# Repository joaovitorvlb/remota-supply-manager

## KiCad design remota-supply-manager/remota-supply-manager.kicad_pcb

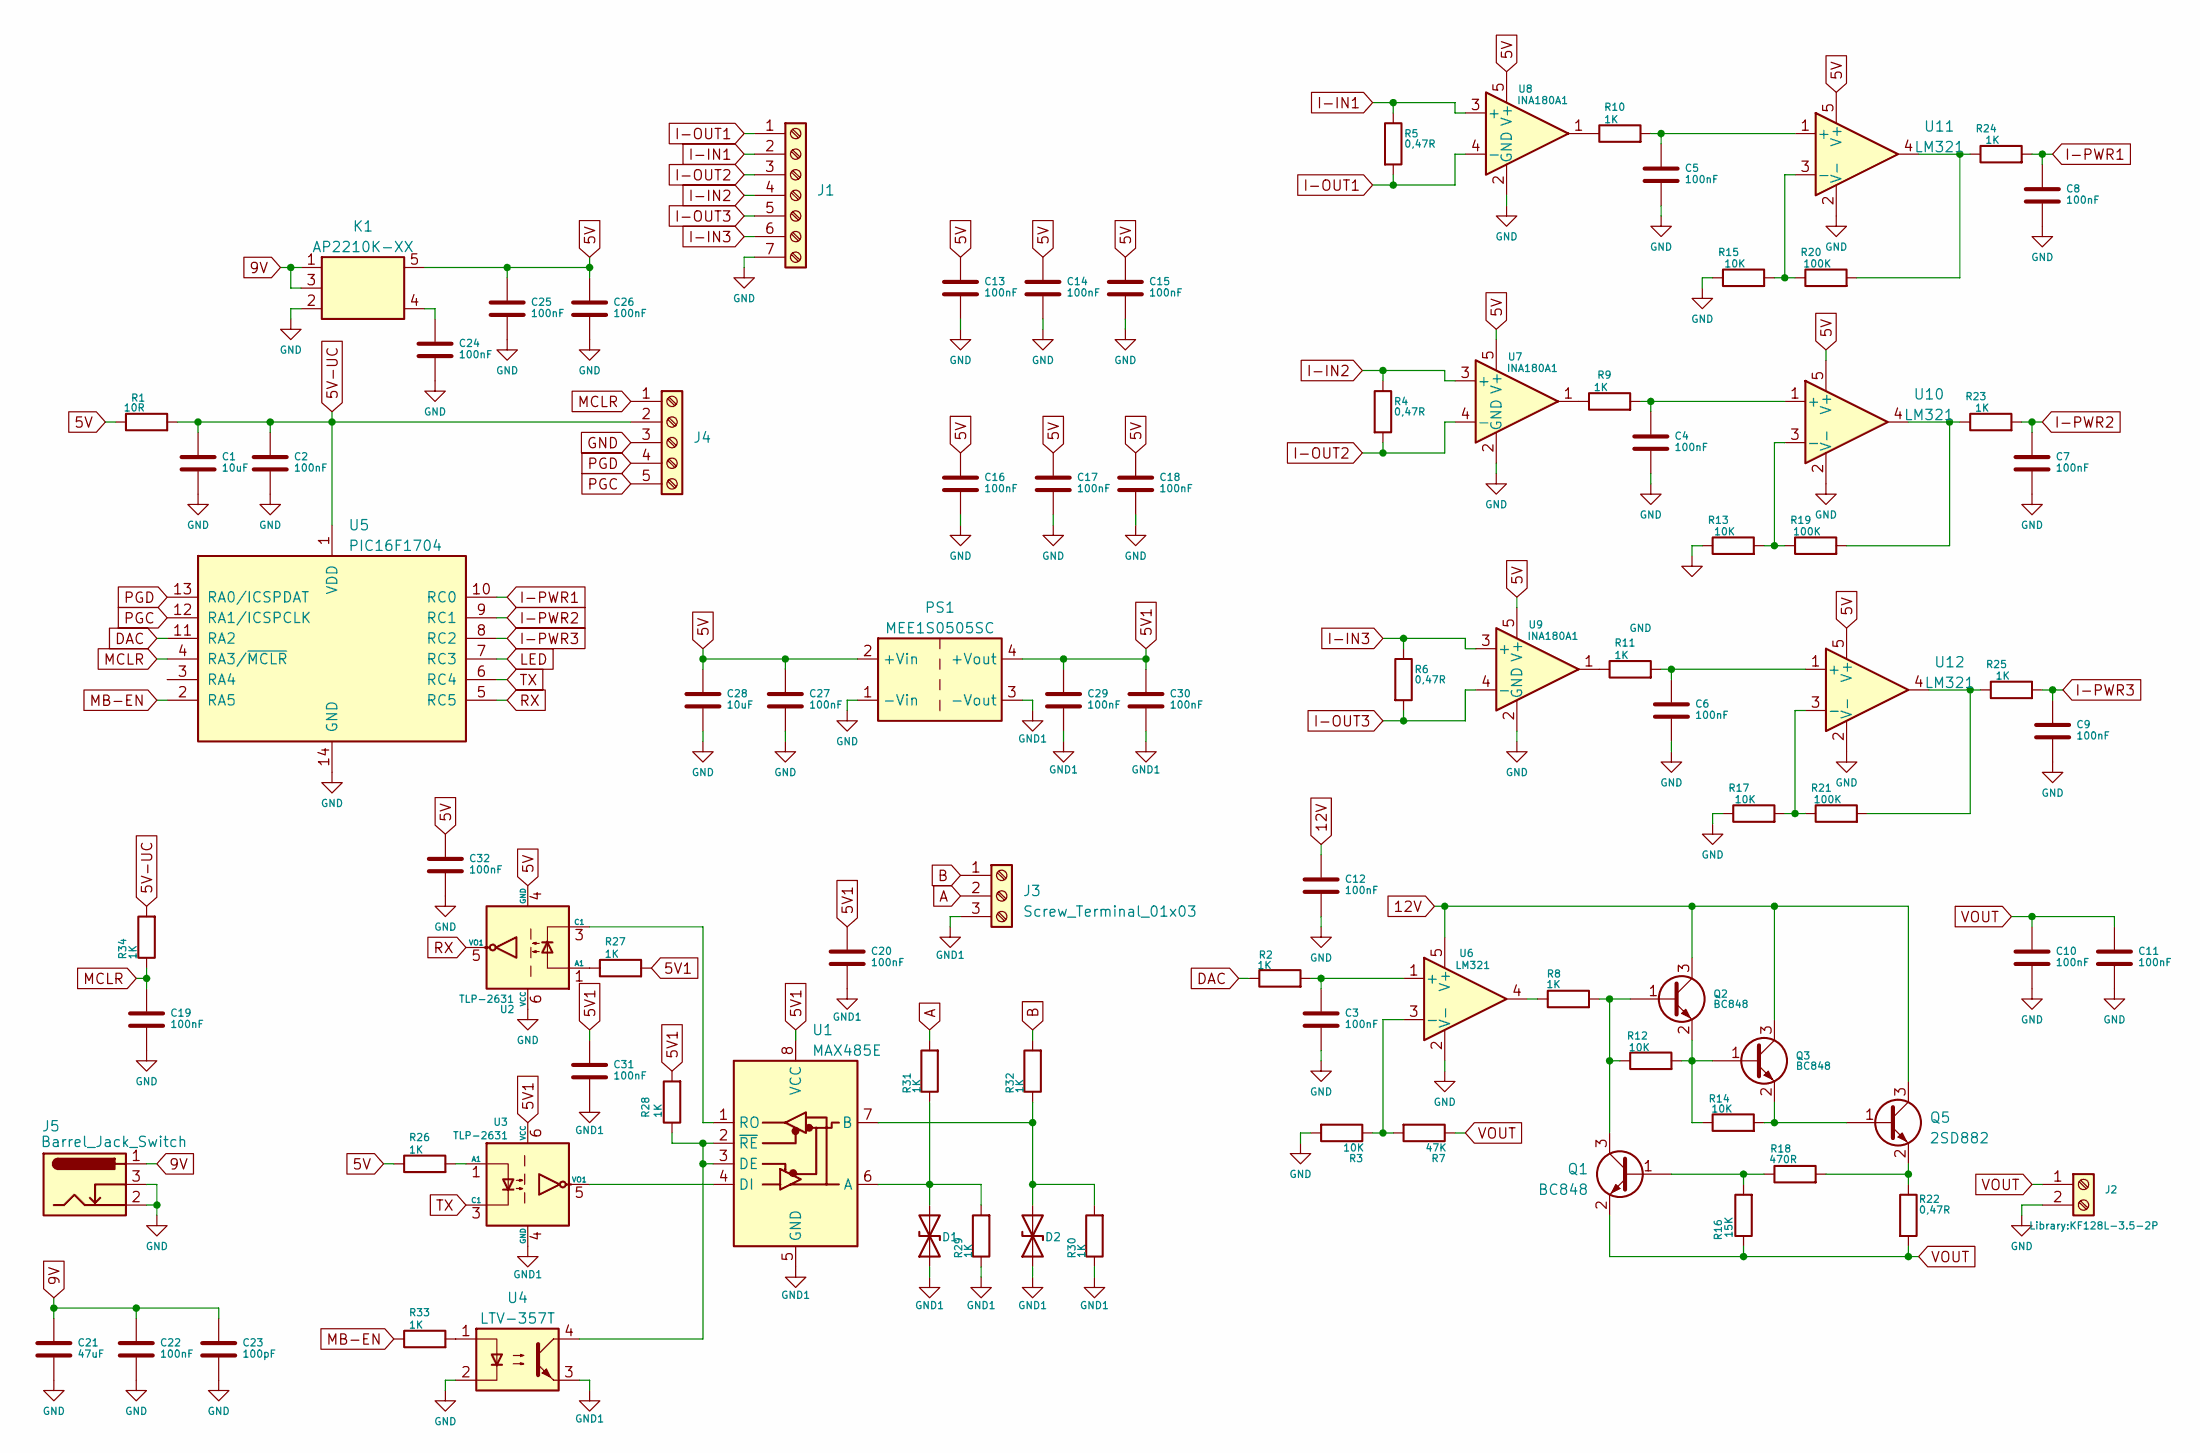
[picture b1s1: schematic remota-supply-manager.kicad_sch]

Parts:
C1, C28: 10uF; C_0805_2012Metric
C2, C3, C4, C5, C6, C7, C8, C9, C10, C11, C12, C13, C14, C15, C16, C17, C18, C19, C20, C22, C24, C25, C26, C27, C29, C30, C31, C32: 100nF; C_0805_2012Metric
C21: 47uF; C_1210_3225Metric
C23: 100pF; C_0805_2012Metric
D1, D2: D_TVS; D_SOD-128
J1: Screw_Terminal_01x07; KF128L-3.5-7P
J2: Screw_Terminal_01x02; KF128L-3.5-2P
J3: Screw_Terminal_01x03; KF128L-3.5-3P
J4: Screw_Terminal_01x05; PinHeader_1x05_P2.54mm_Vertical
J5: Barrel_Jack_Switch; BarrelJack_GCT_DCJ200-10-A_Horizontal
K1: AP2210K-XX; SOT-23-5
PS1: MEE1S0505SC; Converter_DCDC_Murata_MEE1SxxxxSC_THT
Q1, Q2, Q3: BC848; SOT-23
Q5: 2SD882; TO-252-2
R1: 10R; R_1206_3216Metric
R2, R8, R9, R10, R11, R23, R24, R25, R26, R27, R28, R29, R30, R31, R32, R33, R34: 1K; R_0805_2012Metric
R3, R12, R13, R14, R15, R17: 10K; R_0805_2012Metric
R4, R5, R6, R22: 0,47R; R_1206_3216Metric
R7: 47K; R_0805_2012Metric
R16: 15K; R_0805_2012Metric
R18: 470R; R_0805_2012Metric
R19, R20, R21: 100K; R_0805_2012Metric
U1: MAX485E; SO-8_3.9x4.9mm_P1.27mm
U2, U3: TLP-2631; SO-5_4.4x3.6mm_P1.27mm
U4: LTV-357T; SO-4_4.4x3.6mm_P2.54mm
U5: PIC16F1704; SO-14_3.9x8.65mm_P1.27mm
U6, U10, U11, U12: LM321; SOT-23-5
U7, U8, U9: INA180A1; SOT-23-5

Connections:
5V: C13.1, C14.1, C15.1, C16.1, C17.1, C18.1, C25.1, C26.1, C27.1, C28.1, C32.1, K1.5, PS1.2 (+Vin), R1.1, R26.1, U2.4 (GND), U7.5 (V+), U8.5 (V+), U9.5 (V+), U10.5 (V+), U11.5 (V+), U12.5 (V+)
5V1: C20.1, C29.1, C30.1, C31.1, PS1.4 (+Vout), R27.2, R28.2, U1.8 (VCC), U3.6 (VCC)
5V-UC: C1.1, C2.1, J4.2, R1.2, R34.2, U5.1 (VDD)
9V: C21.1, C22.1, C23.1, J5.1, K1.1, K1.3
12V: C12.1, Q2.3 (C), Q3.3 (C), Q5.3 (C), U6.5 (V+)
A: J3.2, R31.2
B: J3.1, R32.2
DAC: R2.1, U5.11 (RA2)
GND: C1.2, C2.2, C3.2, C4.2, C5.2, C6.2, C7.2, C8.2, C9.2, C10.2, C11.2, C12.2, C13.2, C14.2, C15.2, C16.2, C17.2, C18.2, C19.2, C21.2, C22.2, C23.2, C24.2, C25.2, C26.2, C27.2, C28.2, C32.2, J1.7, J2.2, J4.3, J5.2, J5.3, K1.2, PS1.1 (-Vin), R3.2, R13.1, R15.1, R17.1, U2.6 (VCC), U4.2, U5.14 (GND), U6.2 (V-), U7.2 (GND), U8.2 (GND), U9.2 (GND), U10.2 (V-), U11.2 (V-), U12.2 (V-)
GND1: C20.2, C29.2, C30.2, C31.2, D1.1 (A1), D2.1 (A1), J3.3, PS1.3 (-Vout), R29.1, R30.1, U1.5 (GND), U3.4 (GND), U4.3
I-IN1: J1.2, R5.1, U8.3 (+)
I-IN2: J1.4, R4.1, U7.3 (+)
I-IN3: J1.6, R6.1, U9.3 (+)
I-OUT1: J1.1, R5.2, U8.4 (-)
I-OUT2: J1.3, R4.2, U7.4 (-)
I-OUT3: J1.5, R6.2, U9.4 (-)
I-PWR1: C8.1, R24.2, U5.10 (RC0)
I-PWR2: C7.1, R23.2, U5.9 (RC1)
I-PWR3: C9.1, R25.2, U5.8 (RC2)
LED: U5.7 (RC3)
MB-EN: R33.1, U5.2 (RA5)
MCLR: C19.1, J4.1, R34.1, U5.4 (RA3/~MCLR)
unnamed: C24.1, K1.4
unnamed: D1.2 (A2), R29.2, R31.1, U1.6 (A)
unnamed: D2.2 (A2), R30.2, R32.1, U1.7 (B)
unnamed: Q1.1 (B), R16.2, R18.1
unnamed: Q1.3 (C), Q2.1 (B), R8.2, R12.1
unnamed: Q2.2 (E), Q3.1 (B), R12.2, R14.1
unnamed: Q3.2 (E), Q5.1 (B), R14.2
unnamed: Q5.2 (E), R18.2, R22.1
unnamed: R8.1, U6.4
unnamed: R9.1, U7.1
unnamed: R10.1, U8.1
unnamed: R11.1, U9.1
unnamed: R19.2, R23.1, U10.4
unnamed: R20.2, R24.1, U11.4
unnamed: R21.2, R25.1, U12.4
unnamed: R33.2, U4.1
unnamed: R28.1, U1.2 (~RE), U1.3 (DE), U4.4
unnamed: U1.4 (DI), U3.5 (VO1)
unnamed: U1.1 (RO), U2.3 (C1)
unnamed: R27.1, U2.1 (A1)
unnamed: R26.2, U3.1 (A1)
unnamed: C3.1, R2.2, U6.1 (+)
unnamed: R3.1, R7.2, U6.3 (-)
unnamed: C4.1, R9.2, U10.1 (+)
unnamed: R13.2, R19.1, U10.3 (-)
unnamed: C5.1, R10.2, U11.1 (+)
unnamed: R15.2, R20.1, U11.3 (-)
unnamed: C6.1, R11.2, U12.1 (+)
unnamed: R17.2, R21.1, U12.3 (-)
PGC: J4.5, U5.12 (RA1/ICSPCLK)
PGD: J4.4, U5.13 (RA0/ICSPDAT)
RX: U2.5 (VO1), U5.5 (RC5)
TX: U3.3 (C1), U5.6 (RC4)
VOUT: C10.1, C11.1, J2.1, Q1.2 (E), R7.1, R16.1, R22.2

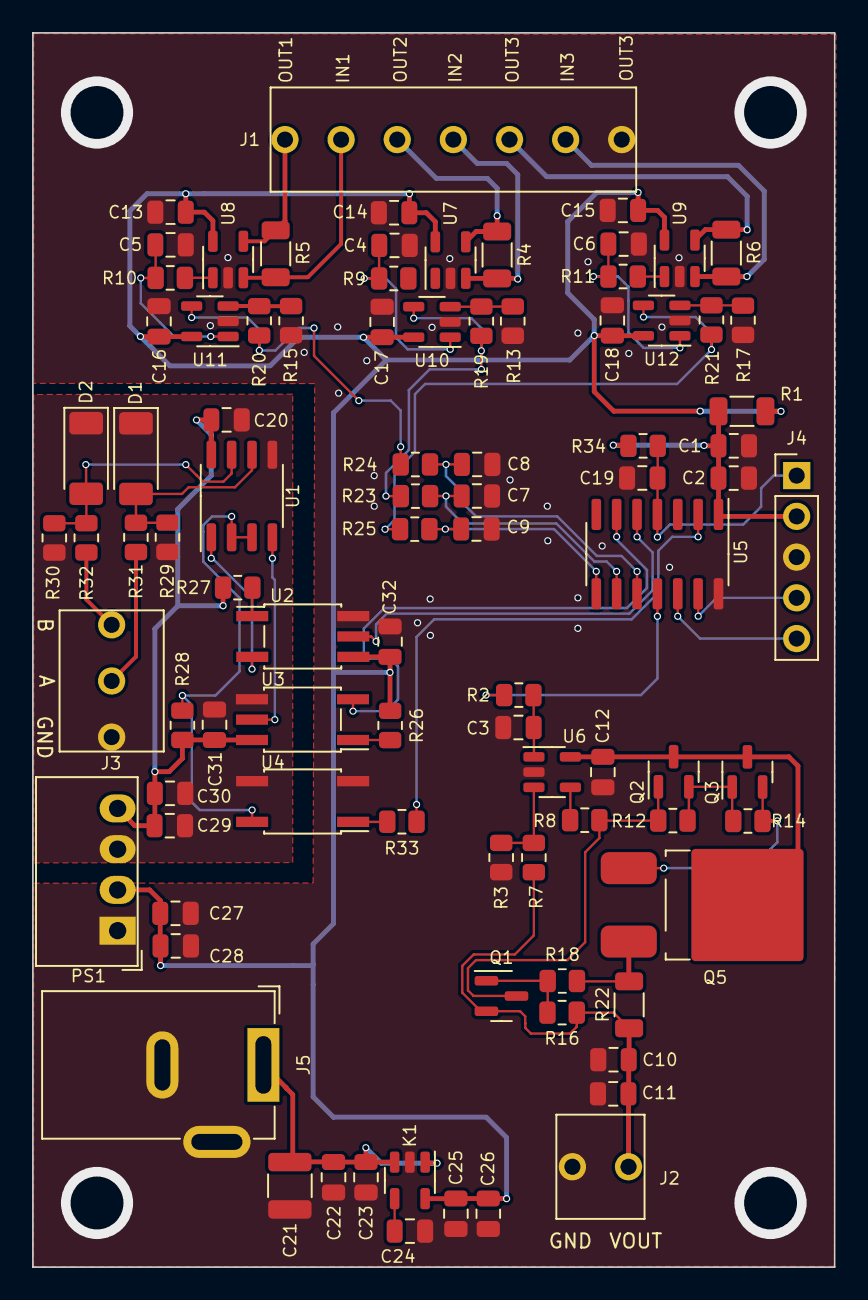
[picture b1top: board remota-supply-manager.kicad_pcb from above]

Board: 2 copper layers, 50.0 x 77.0 mm, 91 parts (0 on the bottom side), 55 nets.

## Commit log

2023-06-22 Preparando para a release v1.0
